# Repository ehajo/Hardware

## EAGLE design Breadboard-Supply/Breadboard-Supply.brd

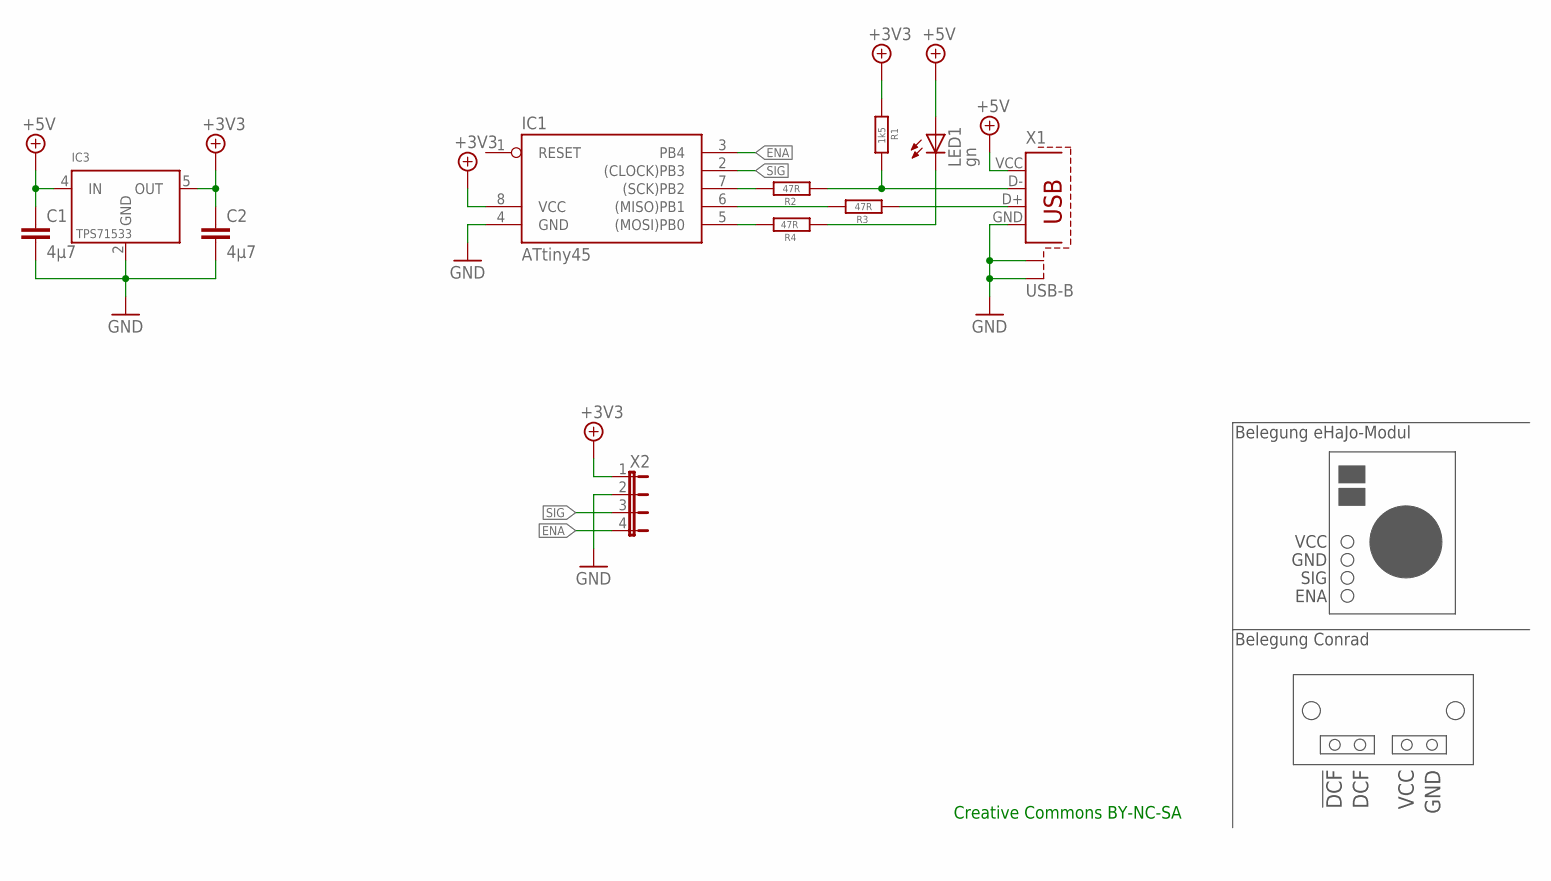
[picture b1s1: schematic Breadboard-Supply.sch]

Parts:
C1, C2: 4µ7; C0805
IC1: ATtiny45; SOIC8
IC3: TPS71533; SOT23-DCK
LED1: gn; CHIP-LED0805
R1: 1k5; R0805
R2, R3, R4: 47R; R0805
X1: USB-B; PN61729-S
X2: JP4E; JP4

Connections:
+3V3: C2.1, IC1.8 (VCC), IC3.5 (OUT), R1.2, X2.1
+5V: C1.1, IC3.4 (IN), LED1.A, X1.VCC
ENA: IC1.3 (PB4), X2.4
GND: C1.2, C2.2, IC1.4 (GND), IC3.2 (GND), X1.GND, X1.S1, X1.S2, X2.2
unnamed: IC1.7 ((SCK)PB2), R2.1
unnamed: IC1.6 ((MISO)PB1), R3.1
unnamed: IC1.5 ((MOSI)PB0), R4.1
unnamed: LED1.C, R4.2
unnamed: R1.1, R2.2, X1.D-
unnamed: R3.2, X1.D+
SIG: IC1.2 ((CLOCK)PB3), X2.3

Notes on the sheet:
Belegung Conrad
VCC
GND
DCF
!DCF
VCC GND SIG ENA
Belegung eHaJo-Modul
Creative Commons BY-NC-SA

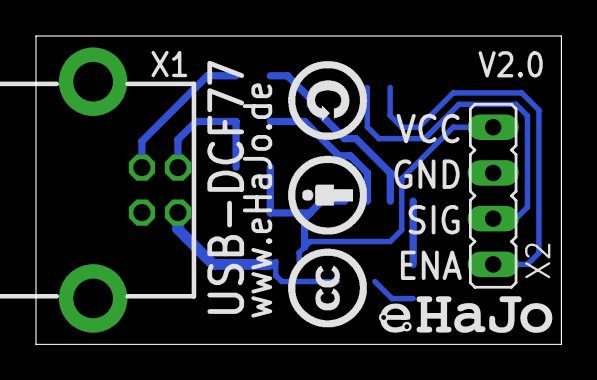
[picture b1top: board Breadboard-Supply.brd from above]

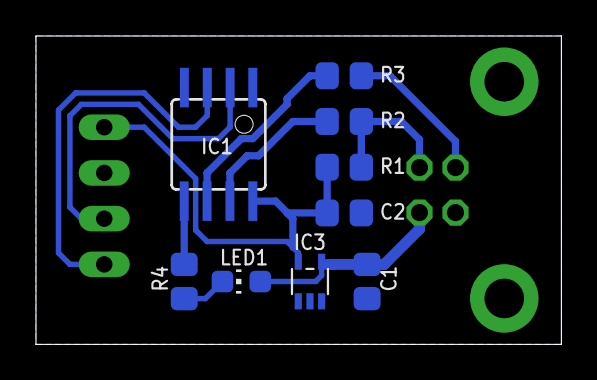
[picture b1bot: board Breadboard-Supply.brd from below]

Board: 1 copper layer, 29.2 x 17.1 mm, 11 parts (9 on the bottom side), 11 nets.

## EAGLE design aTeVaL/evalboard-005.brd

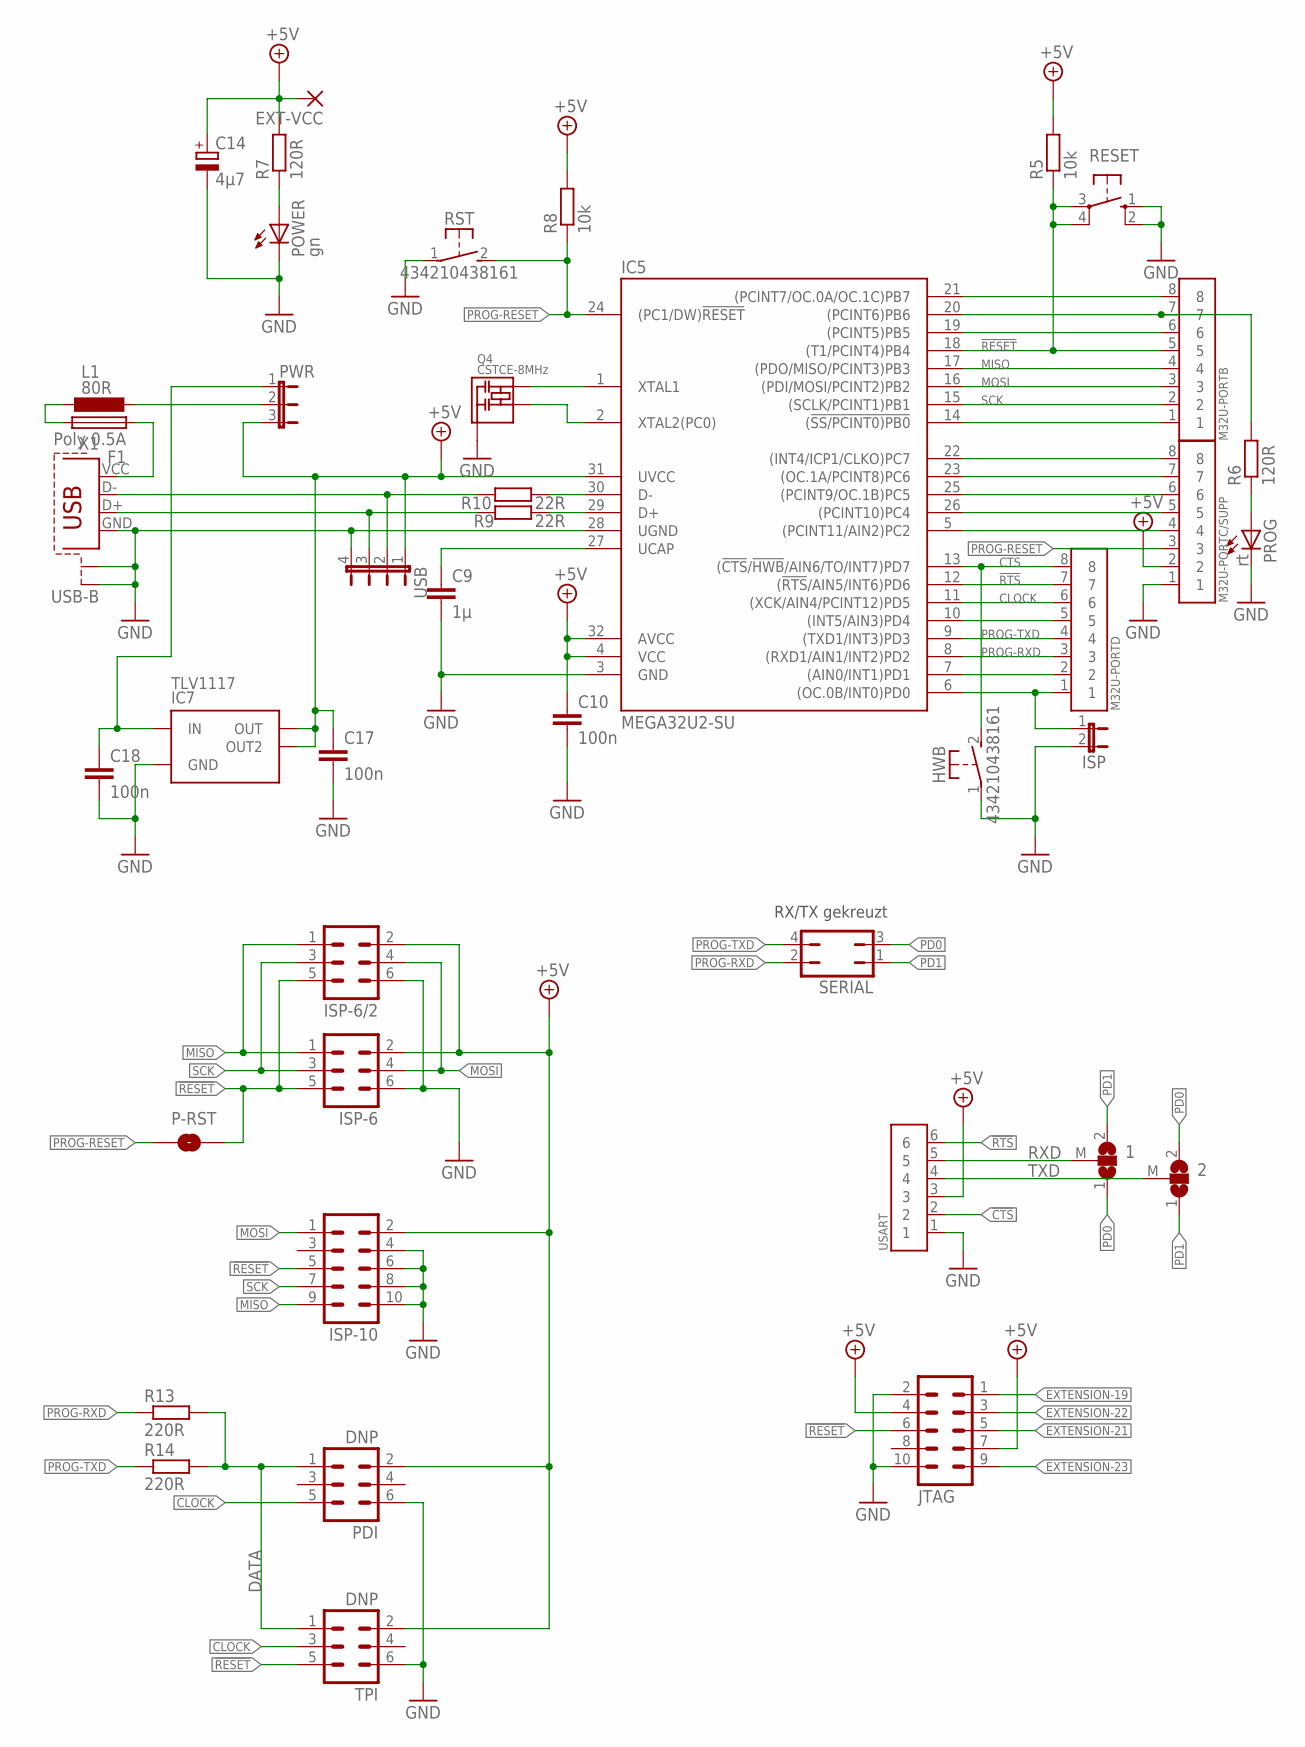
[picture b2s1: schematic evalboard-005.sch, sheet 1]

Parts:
1, 2: SJ2WS; SJ2-S
C9: 1µ; C0805
C10, C17, C18: 100n; C0805
C14: 4µ7; E2,5-6E
EXT-VCC: 2,54/1,0
F1: Poly 0.5A; 1206
HWB: 434210438161; WS-TRS-6,0X3,5
IC5: MEGA32U2-SU; TQFP32-08
IC7: TLV1117; SOT-223-4
ISP: JP1E; JP1
ISP-6, ISP-6/2: ML6
ISP-10: ML10
JTAG: ML10
L1: 80R; L2012C
M32U-PORTB, M32U-PORTC/SUPP, M32U-PORTD: JP8E
P-RST: SJS
PDI: DNP; ML6
POWER: gn; CHIP-LED0805
PROG: rt; CHIP-LED0805
PWR: JP2E; JP2
Q4: CSTCE-8MHz; SMALL-CAP
R5, R8: 10k; R0805
R6, R7: 120R; R0805
R9, R10: 22R; R0805
R13, R14: 220R; R0805
RESET: 10-XX; B3F-10XX
RST: 434210438161; WS-TRS-6,0X3,5
SERIAL: JP2Q
TPI: DNP; ML6
USART: JP6E
USB: JP4E; JP4
X1: USB-B; PN61729-S

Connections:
!CTS: HWB.2 (S), IC5.13 ((!CTS!/!HWB!/AIN6/TO/INT7)PD7), M32U-PORTD.8, USART.2
!RESET: IC5.18 ((T1/PCINT4)PB4), ISP-6.5, ISP-6/2.5, ISP-10.5, JTAG.6, M32U-PORTB.5, P-RST.2, R5.1, RESET.3, RESET.4 (P1), TPI.5; also elsewhere on the board
!RTS: IC5.12 ((!RTS!/AIN5/INT6)PD6), M32U-PORTD.7, USART.6
+5V: C10.1, C14.+, C17.1, EXT-VCC.1, IC5.4 (VCC), IC5.31 (UVCC), IC5.32 (AVCC), IC7.2 (OUT), IC7.4 (OUT2), ISP-6.2, ISP-6/2.2, ISP-10.2, JTAG.4, JTAG.7, M32U-PORTC/SUPP.2, PDI.2, PWR.3, R5.2, R7.2, R8.2, TPI.2, USART.3, USB.1; also elsewhere on the board
CLOCK: IC5.11 ((XCK/AIN4/PCINT12)PD5), M32U-PORTD.6, PDI.5, TPI.3
D+: R9.1, USB.3, X1.D+
D-: R10.1, USB.2, X1.D-
DATA: PDI.1, R13.2, R14.2, TPI.1
EXTENSION-19: JTAG.1; also elsewhere on the board
EXTENSION-21: JTAG.5; also elsewhere on the board
EXTENSION-22: JTAG.3; also elsewhere on the board
EXTENSION-23: JTAG.9; also elsewhere on the board
GND: C9.2, C10.2, C14.-, C17.2, C18.2, HWB.1, IC5.3 (GND), IC5.28 (UGND), IC7.1 (GND), ISP.2, ISP-6.6, ISP-6/2.6, ISP-10.4, ISP-10.6, ISP-10.8, ISP-10.10, JTAG.2, JTAG.10, M32U-PORTC/SUPP.1, PDI.6, POWER.C, PROG.C, Q4.2 (GND), RESET.1 (S), RESET.2 (S1), RST.1, TPI.6, USART.1, USB.4, X1.GND, X1.S1, X1.S2; also elsewhere on the board
MISO: IC5.17 ((PDO/MISO/PCINT3)PB3), ISP-6.1, ISP-6/2.1, ISP-10.9, M32U-PORTB.4; also elsewhere on the board
MOSI: IC5.16 ((PDI/MOSI/PCINT2)PB2), ISP-6.4, ISP-6/2.4, ISP-10.1, M32U-PORTB.3; also elsewhere on the board
unnamed: L1.2, PWR.2
unnamed: F1.1, X1.VCC
unnamed: IC5.14 ((!SS/PCINT0)PB0), M32U-PORTB.1
unnamed: IC5.30 (D-), R10.2
unnamed: IC5.29 (D+), R9.2
unnamed: C9.1, IC5.27 (UCAP)
unnamed: IC5.19 ((PCINT5)PB5), M32U-PORTB.6
unnamed: C18.1, IC7.3 (IN), PWR.1
unnamed: IC5.21 ((PCINT7/OC.0A/OC.1C)PB7), M32U-PORTB.8
unnamed: IC5.10 ((INT5/AIN3)PD4), M32U-PORTD.5
unnamed: IC5.7 ((AIN0/INT1)PD1), M32U-PORTD.2
unnamed: IC5.20 ((PCINT6)PB6), M32U-PORTB.7, R6.2
unnamed: IC5.6 ((OC.0B/INT0)PD0), ISP.1, M32U-PORTD.1
unnamed: IC5.22 ((INT4/ICP1/CLKO)PC7), M32U-PORTC/SUPP.8
unnamed: IC5.23 ((OC.1A/PCINT8)PC6), M32U-PORTC/SUPP.7
unnamed: IC5.25 ((PCINT9/OC.1B)PC5), M32U-PORTC/SUPP.6
unnamed: IC5.26 ((PCINT10)PC4), M32U-PORTC/SUPP.5
unnamed: IC5.5 ((PCINT11/AIN2)PC2), M32U-PORTC/SUPP.4
unnamed: PROG.A, R6.1
unnamed: POWER.A, R7.1
unnamed: F1.2, L1.1
unnamed: IC5.1 (XTAL1), Q4.1 (Q1)
unnamed: IC5.2 (XTAL2(PC0)), Q4.3 (Q2)
PD0: 1.1 (3), 2.2 (1), SERIAL.3; also elsewhere on the board
PD1: 1.2 (1), 2.1 (3), SERIAL.1; also elsewhere on the board
PROG-RESET: IC5.24 ((PC1/DW)!RESET), M32U-PORTC/SUPP.3, P-RST.1, R8.1, RST.2 (S)
PROG-RXD: IC5.8 ((RXD1/AIN1/INT2)PD2), M32U-PORTD.3, R13.1, SERIAL.2
PROG-TXD: IC5.9 ((TXD1/INT3)PD3), M32U-PORTD.4, R14.1, SERIAL.4
RXD: 1.M (2), USART.5
SCK: IC5.15 ((SCLK/PCINT1)PB1), ISP-6.3, ISP-6/2.3, ISP-10.7, M32U-PORTB.2; also elsewhere on the board
TXD: 2.M (2), USART.4

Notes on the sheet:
RX/TX gekreuzt

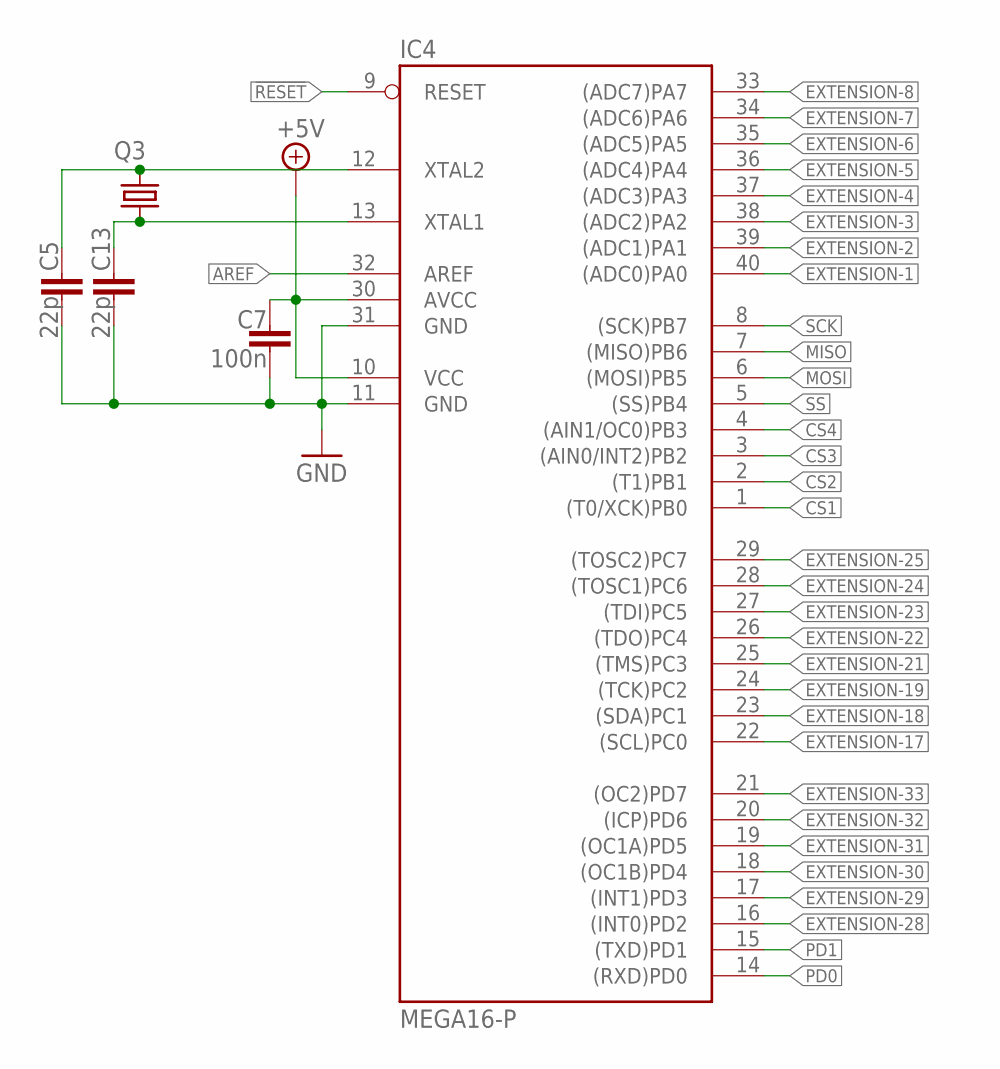
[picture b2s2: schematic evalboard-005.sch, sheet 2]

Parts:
C5, C13: 22p; C0805
C7: 100n; C0805
IC4: MEGA16-P; DIL40
Q3: CRYSTALHC49U70; HC49U70

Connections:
!RESET: IC4.9 (RESET); also elsewhere on the board
+5V: C7.1, IC4.10 (VCC), IC4.30 (AVCC); also elsewhere on the board
AREF: IC4.32 (AREF); also elsewhere on the board
CS1: IC4.1 ((T0/XCK)PB0); also elsewhere on the board
CS2: IC4.2 ((T1)PB1); also elsewhere on the board
CS3: IC4.3 ((AIN0/INT2)PB2); also elsewhere on the board
CS4: IC4.4 ((AIN1/OC0)PB3); also elsewhere on the board
EXTENSION-1: IC4.40 ((ADC0)PA0); also elsewhere on the board
EXTENSION-2: IC4.39 ((ADC1)PA1); also elsewhere on the board
EXTENSION-3: IC4.38 ((ADC2)PA2); also elsewhere on the board
EXTENSION-4: IC4.37 ((ADC3)PA3); also elsewhere on the board
EXTENSION-5: IC4.36 ((ADC4)PA4); also elsewhere on the board
EXTENSION-6: IC4.35 ((ADC5)PA5); also elsewhere on the board
EXTENSION-7: IC4.34 ((ADC6)PA6); also elsewhere on the board
EXTENSION-8: IC4.33 ((ADC7)PA7); also elsewhere on the board
EXTENSION-17: IC4.22 ((SCL)PC0); also elsewhere on the board
EXTENSION-18: IC4.23 ((SDA)PC1); also elsewhere on the board
EXTENSION-19: IC4.24 ((TCK)PC2); also elsewhere on the board
EXTENSION-21: IC4.25 ((TMS)PC3); also elsewhere on the board
EXTENSION-22: IC4.26 ((TDO)PC4); also elsewhere on the board
EXTENSION-23: IC4.27 ((TDI)PC5); also elsewhere on the board
EXTENSION-24: IC4.28 ((TOSC1)PC6); also elsewhere on the board
EXTENSION-25: IC4.29 ((TOSC2)PC7); also elsewhere on the board
EXTENSION-28: IC4.16 ((INT0)PD2); also elsewhere on the board
EXTENSION-29: IC4.17 ((INT1)PD3); also elsewhere on the board
EXTENSION-30: IC4.18 ((OC1B)PD4); also elsewhere on the board
EXTENSION-31: IC4.19 ((OC1A)PD5); also elsewhere on the board
EXTENSION-32: IC4.20 ((ICP)PD6); also elsewhere on the board
EXTENSION-33: IC4.21 ((OC2)PD7); also elsewhere on the board
GND: C5.2, C7.2, C13.2, IC4.11 (GND), IC4.31 (GND); also elsewhere on the board
MISO: IC4.7 ((MISO)PB6); also elsewhere on the board
MOSI: IC4.6 ((MOSI)PB5); also elsewhere on the board
unnamed: C5.1, IC4.12 (XTAL2), Q3.2
unnamed: C13.1, IC4.13 (XTAL1), Q3.1
PD0: IC4.14 ((RXD)PD0); also elsewhere on the board
PD1: IC4.15 ((TXD)PD1); also elsewhere on the board
SCK: IC4.8 ((SCK)PB7); also elsewhere on the board
SS: IC4.5 ((SS)PB4); also elsewhere on the board

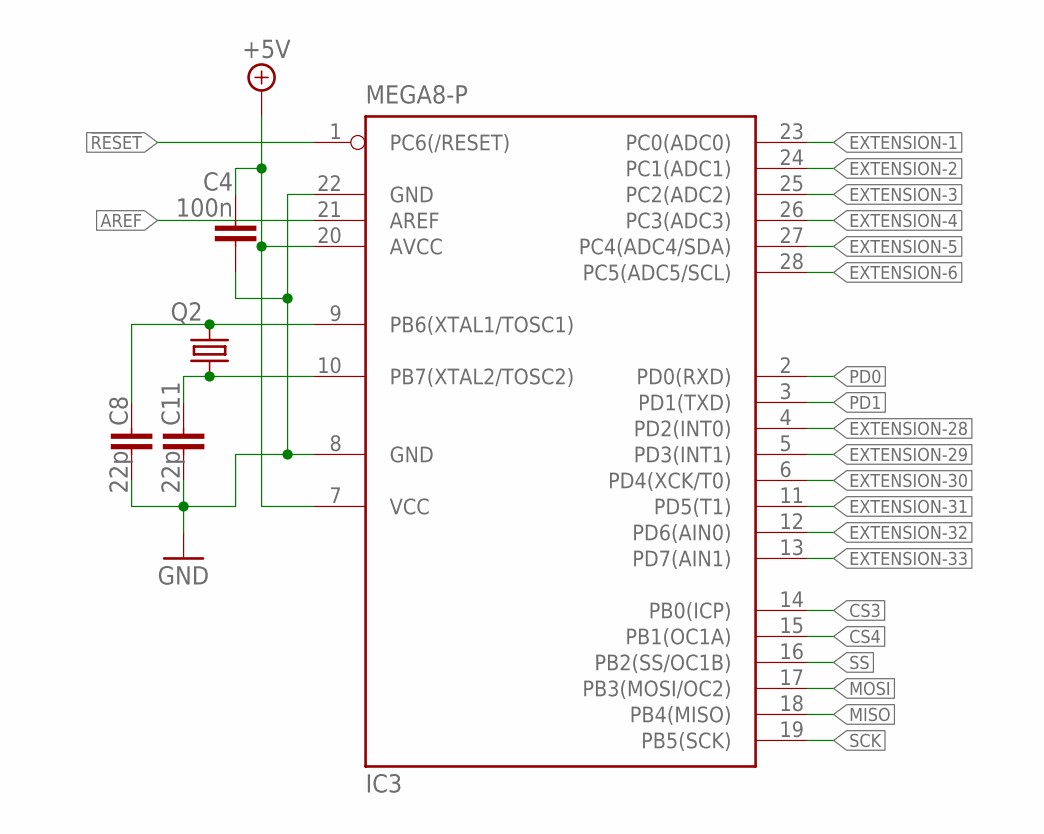
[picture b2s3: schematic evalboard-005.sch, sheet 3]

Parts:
C4: 100n; C0805
C8, C11: 22p; C0805
IC3: MEGA8-P; DIL28-3
Q2: CRYSTALHC49U70; HC49U70

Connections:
!RESET: IC3.1 (PC6(/RESET)); also elsewhere on the board
+5V: C4.1, IC3.7 (VCC), IC3.20 (AVCC); also elsewhere on the board
AREF: IC3.21 (AREF); also elsewhere on the board
CS3: IC3.14 (PB0(ICP)); also elsewhere on the board
CS4: IC3.15 (PB1(OC1A)); also elsewhere on the board
EXTENSION-1: IC3.23 (PC0(ADC0)); also elsewhere on the board
EXTENSION-2: IC3.24 (PC1(ADC1)); also elsewhere on the board
EXTENSION-3: IC3.25 (PC2(ADC2)); also elsewhere on the board
EXTENSION-4: IC3.26 (PC3(ADC3)); also elsewhere on the board
EXTENSION-5: IC3.27 (PC4(ADC4/SDA)); also elsewhere on the board
EXTENSION-6: IC3.28 (PC5(ADC5/SCL)); also elsewhere on the board
EXTENSION-28: IC3.4 (PD2(INT0)); also elsewhere on the board
EXTENSION-29: IC3.5 (PD3(INT1)); also elsewhere on the board
EXTENSION-30: IC3.6 (PD4(XCK/T0)); also elsewhere on the board
EXTENSION-31: IC3.11 (PD5(T1)); also elsewhere on the board
EXTENSION-32: IC3.12 (PD6(AIN0)); also elsewhere on the board
EXTENSION-33: IC3.13 (PD7(AIN1)); also elsewhere on the board
GND: C4.2, C8.2, C11.2, IC3.8 (GND), IC3.22 (GND); also elsewhere on the board
MISO: IC3.18 (PB4(MISO)); also elsewhere on the board
MOSI: IC3.17 (PB3(MOSI/OC2)); also elsewhere on the board
unnamed: C8.1, IC3.9 (PB6(XTAL1/TOSC1)), Q2.2
unnamed: C11.1, IC3.10 (PB7(XTAL2/TOSC2)), Q2.1
PD0: IC3.2 (PD0(RXD)); also elsewhere on the board
PD1: IC3.3 (PD1(TXD)); also elsewhere on the board
SCK: IC3.19 (PB5(SCK)); also elsewhere on the board
SS: IC3.16 (PB2(SS/OC1B)); also elsewhere on the board

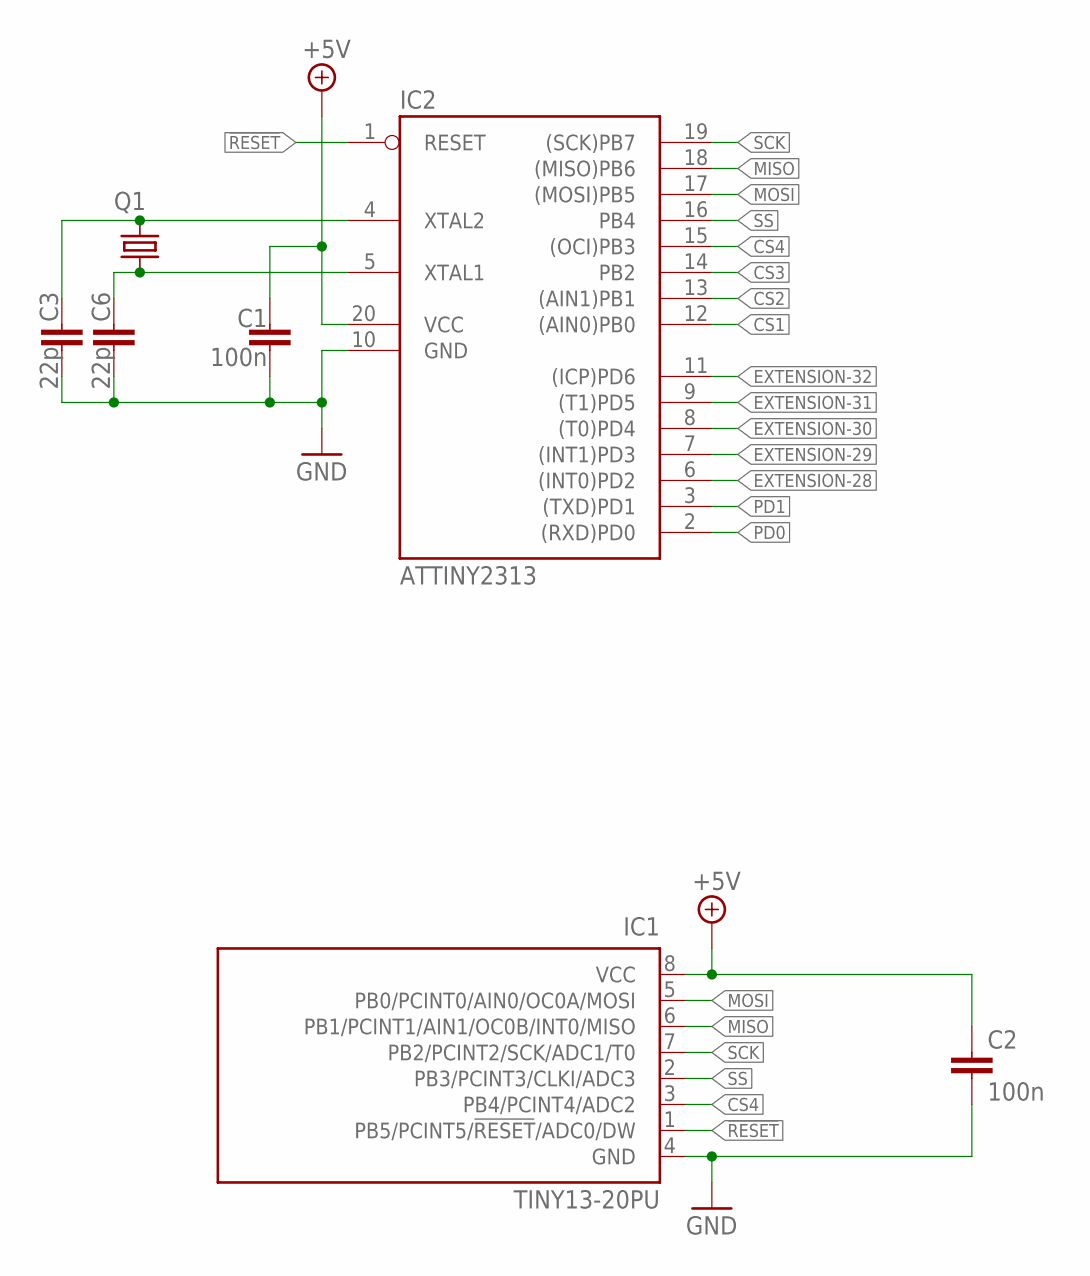
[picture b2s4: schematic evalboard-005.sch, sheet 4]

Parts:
C1, C2: 100n; C0805
C3, C6: 22p; C0805
IC1: TINY13-20PU; DIL08
IC2: ATTINY2313; DIL20
Q1: CRYSTALHC49U70; HC49U70

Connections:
!RESET: IC1.1 (PB5/PCINT5/!RESET!/ADC0/DW), IC2.1 (RESET); also elsewhere on the board
+5V: C1.1, C2.1, IC1.8 (VCC), IC2.20 (VCC); also elsewhere on the board
CS1: IC2.12 ((AIN0)PB0); also elsewhere on the board
CS2: IC2.13 ((AIN1)PB1); also elsewhere on the board
CS3: IC2.14 (PB2); also elsewhere on the board
CS4: IC1.3 (PB4/PCINT4/ADC2), IC2.15 ((OCI)PB3); also elsewhere on the board
EXTENSION-28: IC2.6 ((INT0)PD2); also elsewhere on the board
EXTENSION-29: IC2.7 ((INT1)PD3); also elsewhere on the board
EXTENSION-30: IC2.8 ((T0)PD4); also elsewhere on the board
EXTENSION-31: IC2.9 ((T1)PD5); also elsewhere on the board
EXTENSION-32: IC2.11 ((ICP)PD6); also elsewhere on the board
GND: C1.2, C2.2, C3.2, C6.2, IC1.4 (GND), IC2.10 (GND); also elsewhere on the board
MISO: IC1.6 (PB1/PCINT1/AIN1/OC0B/INT0/MISO), IC2.18 ((MISO)PB6); also elsewhere on the board
MOSI: IC1.5 (PB0/PCINT0/AIN0/OC0A/MOSI), IC2.17 ((MOSI)PB5); also elsewhere on the board
unnamed: C3.1, IC2.4 (XTAL2), Q1.2
unnamed: C6.1, IC2.5 (XTAL1), Q1.1
PD0: IC2.2 ((RXD)PD0); also elsewhere on the board
PD1: IC2.3 ((TXD)PD1); also elsewhere on the board
SCK: IC1.7 (PB2/PCINT2/SCK/ADC1/T0), IC2.19 ((SCK)PB7); also elsewhere on the board
SS: IC1.2 (PB3/PCINT3/CLKI/ADC3), IC2.16 (PB4); also elsewhere on the board

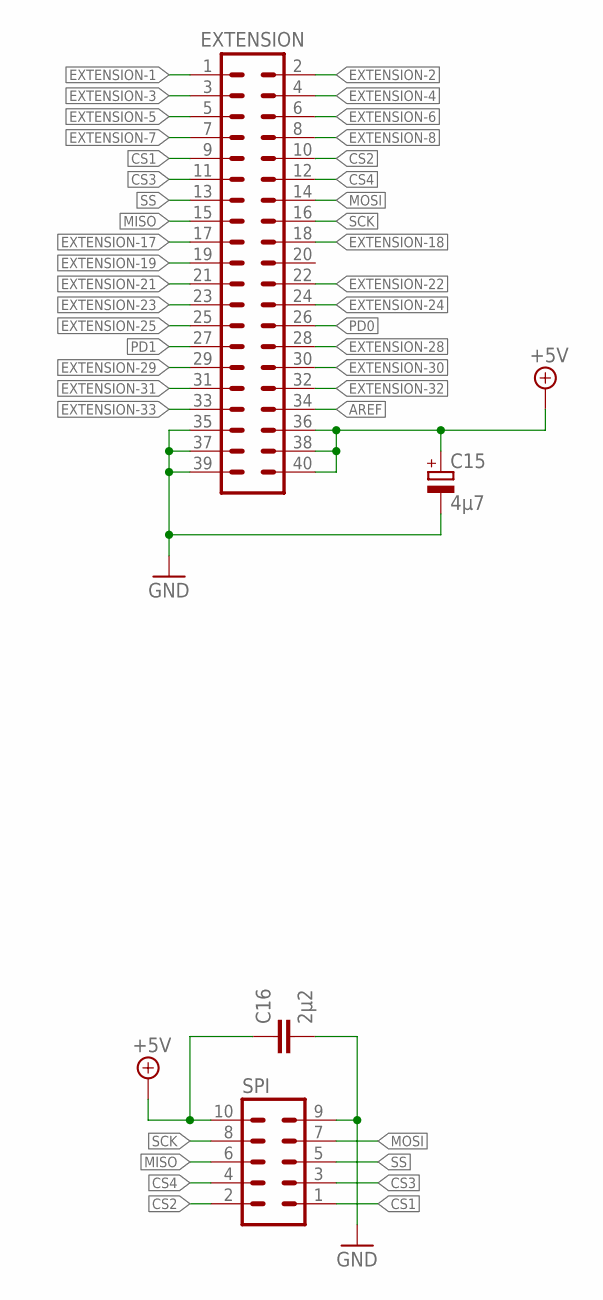
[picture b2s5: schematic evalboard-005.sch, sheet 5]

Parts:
C15: 4µ7; E2,5-6E
C16: 2µ2; C0805
EXTENSION: ML40
SPI: ML10

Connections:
+5V: C15.+, C16.1, EXTENSION.36, EXTENSION.38, EXTENSION.40, SPI.10; also elsewhere on the board
AREF: EXTENSION.34; also elsewhere on the board
CS1: EXTENSION.9, SPI.1; also elsewhere on the board
CS2: EXTENSION.10, SPI.2; also elsewhere on the board
CS3: EXTENSION.11, SPI.3; also elsewhere on the board
CS4: EXTENSION.12, SPI.4; also elsewhere on the board
EXTENSION-1: EXTENSION.1; also elsewhere on the board
EXTENSION-2: EXTENSION.2; also elsewhere on the board
EXTENSION-3: EXTENSION.3; also elsewhere on the board
EXTENSION-4: EXTENSION.4; also elsewhere on the board
EXTENSION-5: EXTENSION.5; also elsewhere on the board
EXTENSION-6: EXTENSION.6; also elsewhere on the board
EXTENSION-7: EXTENSION.7; also elsewhere on the board
EXTENSION-8: EXTENSION.8; also elsewhere on the board
EXTENSION-17: EXTENSION.17; also elsewhere on the board
EXTENSION-18: EXTENSION.18; also elsewhere on the board
EXTENSION-19: EXTENSION.19; also elsewhere on the board
EXTENSION-21: EXTENSION.21; also elsewhere on the board
EXTENSION-22: EXTENSION.22; also elsewhere on the board
EXTENSION-23: EXTENSION.23; also elsewhere on the board
EXTENSION-24: EXTENSION.24; also elsewhere on the board
EXTENSION-25: EXTENSION.25; also elsewhere on the board
EXTENSION-28: EXTENSION.28; also elsewhere on the board
EXTENSION-29: EXTENSION.29; also elsewhere on the board
EXTENSION-30: EXTENSION.30; also elsewhere on the board
EXTENSION-31: EXTENSION.31; also elsewhere on the board
EXTENSION-32: EXTENSION.32; also elsewhere on the board
EXTENSION-33: EXTENSION.33; also elsewhere on the board
GND: C15.-, C16.2, EXTENSION.35, EXTENSION.37, EXTENSION.39, SPI.9; also elsewhere on the board
MISO: EXTENSION.15, SPI.6; also elsewhere on the board
MOSI: EXTENSION.14, SPI.7; also elsewhere on the board
PD0: EXTENSION.26; also elsewhere on the board
PD1: EXTENSION.27; also elsewhere on the board
SCK: EXTENSION.16, SPI.8; also elsewhere on the board
SS: EXTENSION.13, SPI.5; also elsewhere on the board

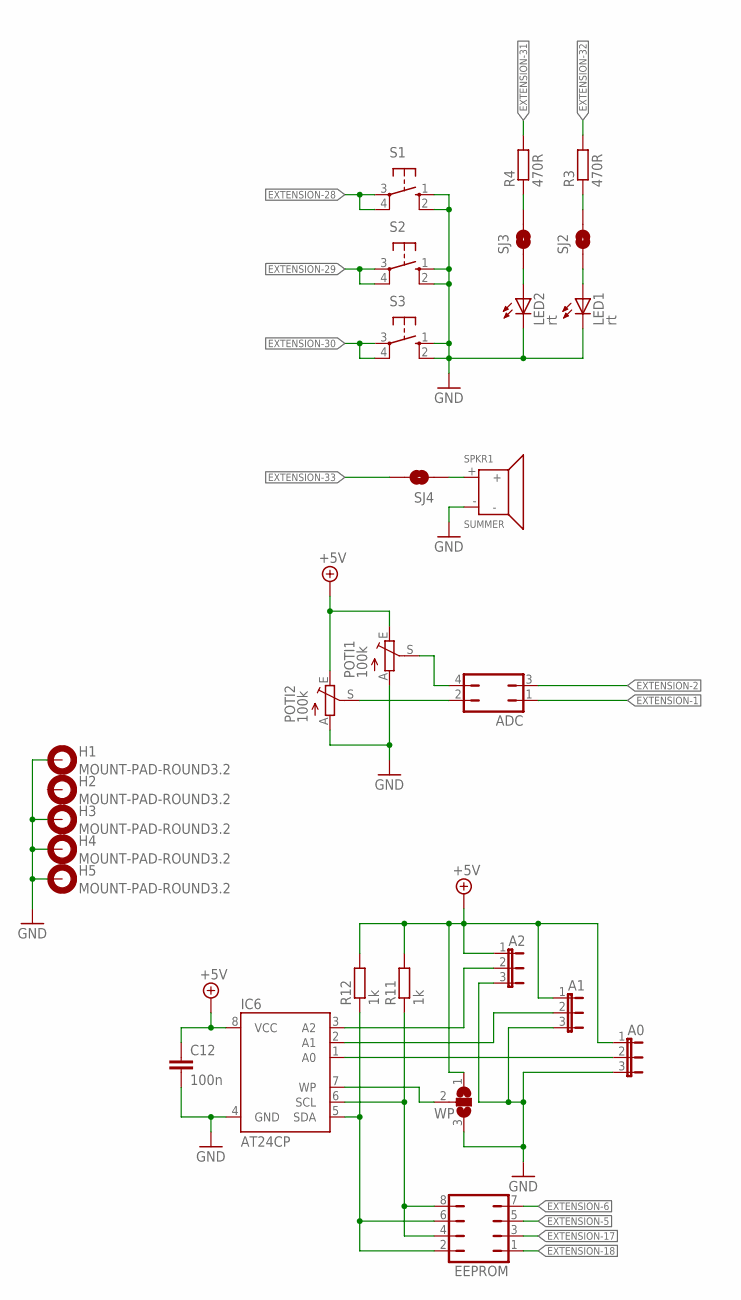
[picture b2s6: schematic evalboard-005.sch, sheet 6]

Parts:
A0, A1, A2: JP2E; JP2
ADC: JP2Q
C12: 100n; C0805
EEPROM: JP4Q
H1, H2, H3, H4, H5: MOUNT-PAD-ROUND3.2; 3,2-PAD
IC6: AT24CP; DIL08
LED1, LED2: rt; LED5MM
POTI1, POTI2: 100k; PT-6
R3, R4: 470R; R0805
R11, R12: 1k; R0805
S1, S2, S3: 10-XX; B3F-10XX
SJ2, SJ3, SJ4: SJS
SPKR1: SUMMER
WP: SJ2W; SJ_2

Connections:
+5V: A0.1, A1.1, A2.1, C12.1, IC6.8 (VCC), POTI1.E, POTI2.E, R11.2, R12.2, WP.1; also elsewhere on the board
A0: A0.2, IC6.1 (A0)
EXTENSION-1: ADC.1; also elsewhere on the board
EXTENSION-2: ADC.3; also elsewhere on the board
EXTENSION-5: EEPROM.5; also elsewhere on the board
EXTENSION-6: EEPROM.7; also elsewhere on the board
EXTENSION-17: EEPROM.3; also elsewhere on the board
EXTENSION-18: EEPROM.1; also elsewhere on the board
EXTENSION-28: S1.3, S1.4 (P1); also elsewhere on the board
EXTENSION-29: S2.3, S2.4 (P1); also elsewhere on the board
EXTENSION-30: S3.3, S3.4 (P1); also elsewhere on the board
EXTENSION-31: R4.2; also elsewhere on the board
EXTENSION-32: R3.2; also elsewhere on the board
EXTENSION-33: SJ4.2; also elsewhere on the board
GND: A0.3, A1.3, A2.3, C12.2, H1.B3,2, H3.B3,2, H4.B3,2, H5.B3,2, IC6.4 (GND), LED1.K (C), LED2.K (C), POTI1.A, POTI2.A, S1.1 (S), S1.2 (S1), S2.1 (S), S2.2 (S1), S3.1 (S), S3.2 (S1), SPKR1.-, WP.3; also elsewhere on the board
unnamed: R4.1, SJ3.2
unnamed: R3.1, SJ2.2
unnamed: A2.2, IC6.3 (A2)
unnamed: A1.2, IC6.2 (A1)
unnamed: EEPROM.2, EEPROM.6, IC6.5 (SDA), R12.1
unnamed: EEPROM.4, EEPROM.8, IC6.6 (SCL), R11.1
unnamed: ADC.4, POTI1.S
unnamed: ADC.2, POTI2.S
unnamed: IC6.7 (WP), WP.2
unnamed: LED2.A, SJ3.1
unnamed: LED1.A, SJ2.1
unnamed: SJ4.1, SPKR1.+

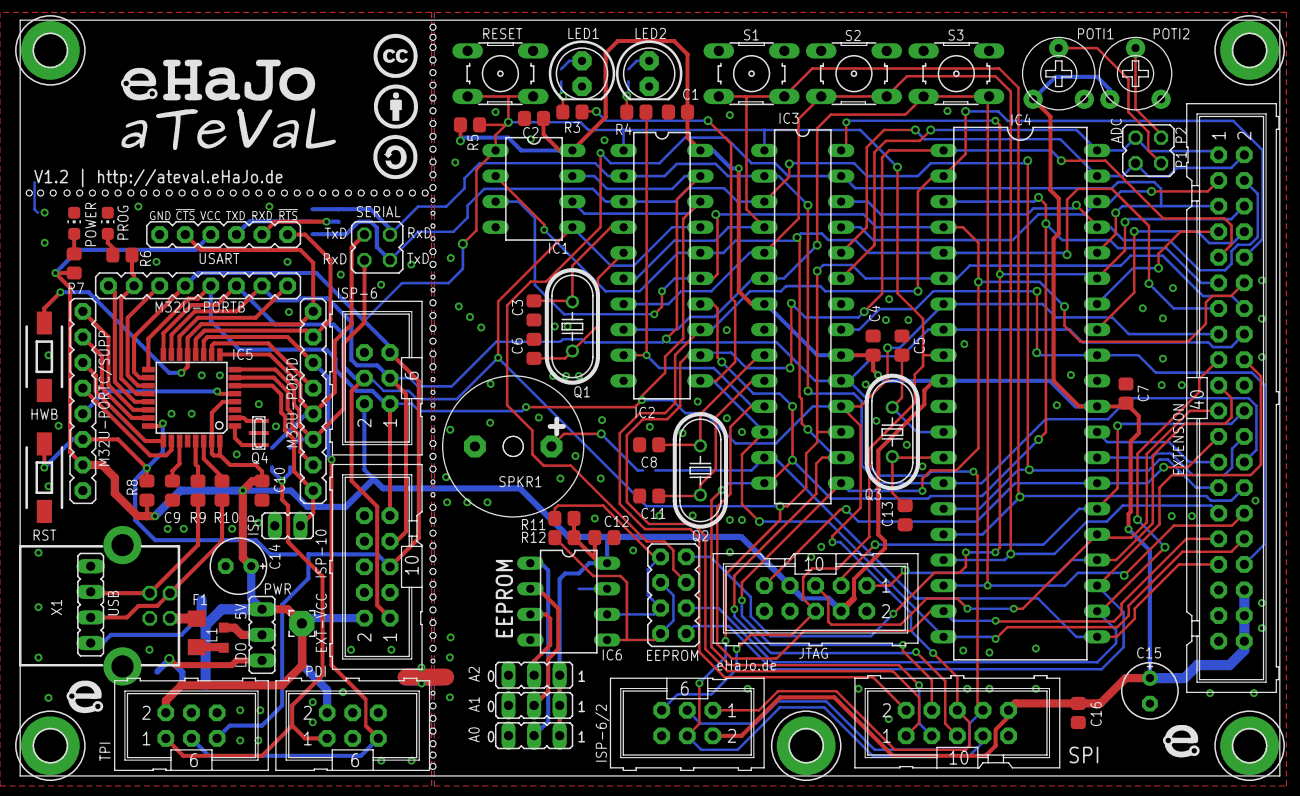
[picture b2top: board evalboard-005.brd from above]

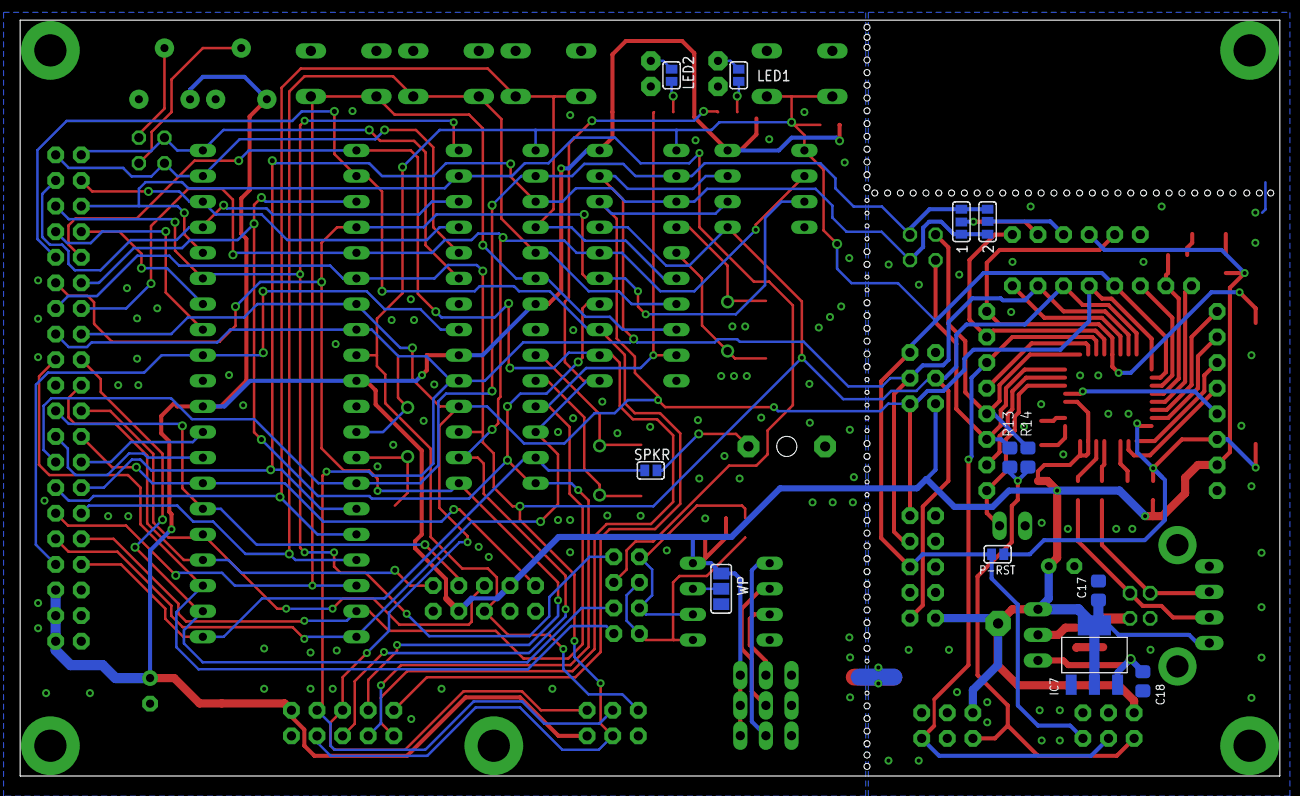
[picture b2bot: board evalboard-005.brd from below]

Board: 2 copper layers, 125.0 x 75.0 mm, 91 parts (12 on the bottom side), 89 nets.

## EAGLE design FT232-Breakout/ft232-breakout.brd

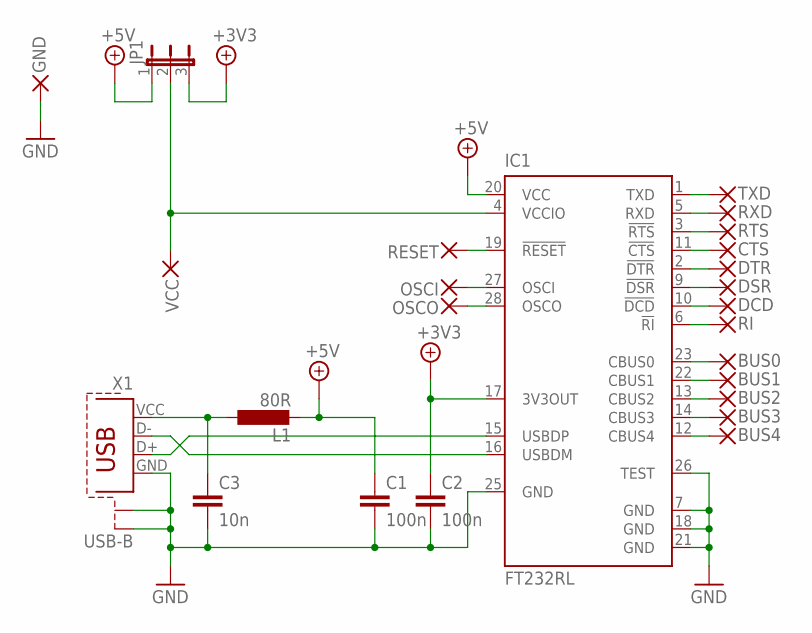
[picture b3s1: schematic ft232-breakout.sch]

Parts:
BUS0, BUS1, BUS2, BUS3, BUS4: WIREPAD2,15/1,0; 2,15/1,0
C1, C2: 100n; C0805
C3: 10n; C0805
CTS: WIREPAD2,15/1,0; 2,15/1,0
DCD: WIREPAD2,15/1,0; 2,15/1,0
DSR: WIREPAD2,15/1,0; 2,15/1,0
DTR: WIREPAD2,15/1,0; 2,15/1,0
GND: WIREPAD2,15/1,0; 2,15/1,0
IC1: FT232RL; SSOP28
JP1: JP2E; JP2
L1: 80R; L2012C
OSCI: WIREPAD2,15/1,0; 2,15/1,0
OSCO: WIREPAD2,15/1,0; 2,15/1,0
RESET: WIREPAD2,15/1,0; 2,15/1,0
RI: WIREPAD2,15/1,0; 2,15/1,0
RTS: WIREPAD2,15/1,0; 2,15/1,0
RXD: WIREPAD2,15/1,0; 2,15/1,0
TXD: WIREPAD2,15/1,0; 2,15/1,0
VCC: WIREPAD2,15/1,0; 2,15/1,0
X1: USB-B; PN61729-S

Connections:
+3V3: C2.1, IC1.17 (3V3OUT), JP1.3
+5V: C1.1, IC1.20 (VCC), JP1.1, L1.2
GND: C1.2, C2.2, C3.2, GND.1, IC1.7 (GND), IC1.18 (GND), IC1.21 (GND), IC1.25 (GND), IC1.26 (TEST), X1.GND, X1.S1, X1.S2
unnamed: IC1.16 (USBDM), X1.D-
unnamed: IC1.15 (USBDP), X1.D+
unnamed: BUS3.1, IC1.14 (CBUS3)
unnamed: C3.1, L1.1, X1.VCC
unnamed: BUS2.1, IC1.13 (CBUS2)
unnamed: BUS1.1, IC1.22 (CBUS1)
unnamed: BUS0.1, IC1.23 (CBUS0)
unnamed: IC1.6 (!RI), RI.1
unnamed: BUS4.1, IC1.12 (CBUS4)
unnamed: DCD.1, IC1.10 (!DCD)
unnamed: DSR.1, IC1.9 (!DSR)
unnamed: DTR.1, IC1.2 (!DTR)
unnamed: CTS.1, IC1.11 (!CTS)
unnamed: IC1.3 (!RTS), RTS.1
unnamed: IC1.5 (RXD), RXD.1
unnamed: IC1.1 (TXD), TXD.1
unnamed: IC1.19 (!RESET), RESET.1
unnamed: IC1.27 (OSCI), OSCI.1
unnamed: IC1.28 (OSCO), OSCO.1
unnamed: IC1.4 (VCCIO), JP1.2, VCC.1

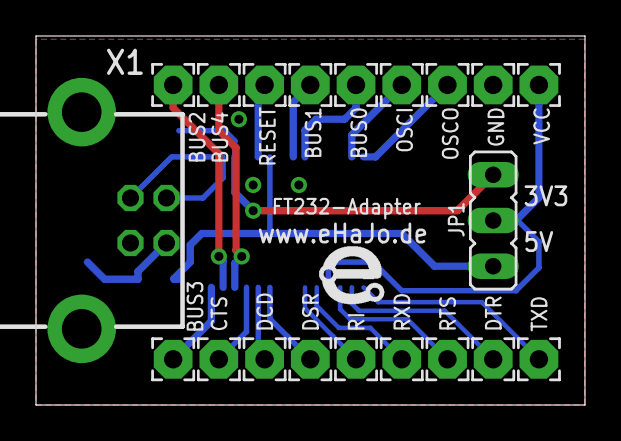
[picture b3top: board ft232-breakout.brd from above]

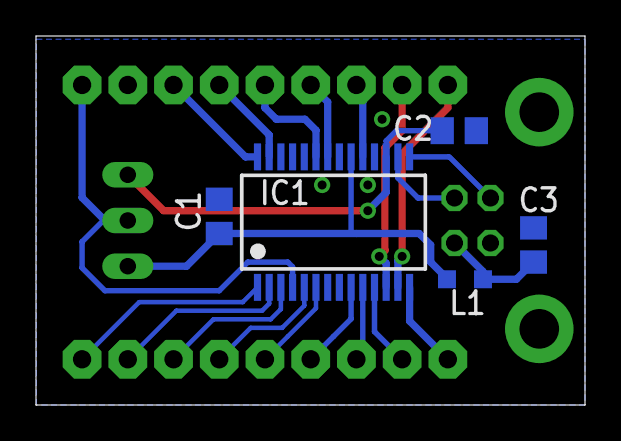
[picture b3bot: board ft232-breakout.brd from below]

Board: 2 copper layers, 30.5 x 20.5 mm, 25 parts (5 on the bottom side), 23 nets.
